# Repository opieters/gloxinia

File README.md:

Gloxinia
========

Open-source release of code and PCB-design files of the Gloxinia platform.

Building the code requires MPLAB X 1.35 or above and KiCAD 5.0.2 or above. 

Citing
------

If you use this code for a scientific publication, please consider citing our paper [_Gloxinia—An Open-Source Sensing Platform to Monitor the Dynamic Responses of Plants_](https://doi.org/10.3390/s20113055).

Licence
-------

GNU GPLv3 4.0

A copy of the licence can be found in `LICENCE`.

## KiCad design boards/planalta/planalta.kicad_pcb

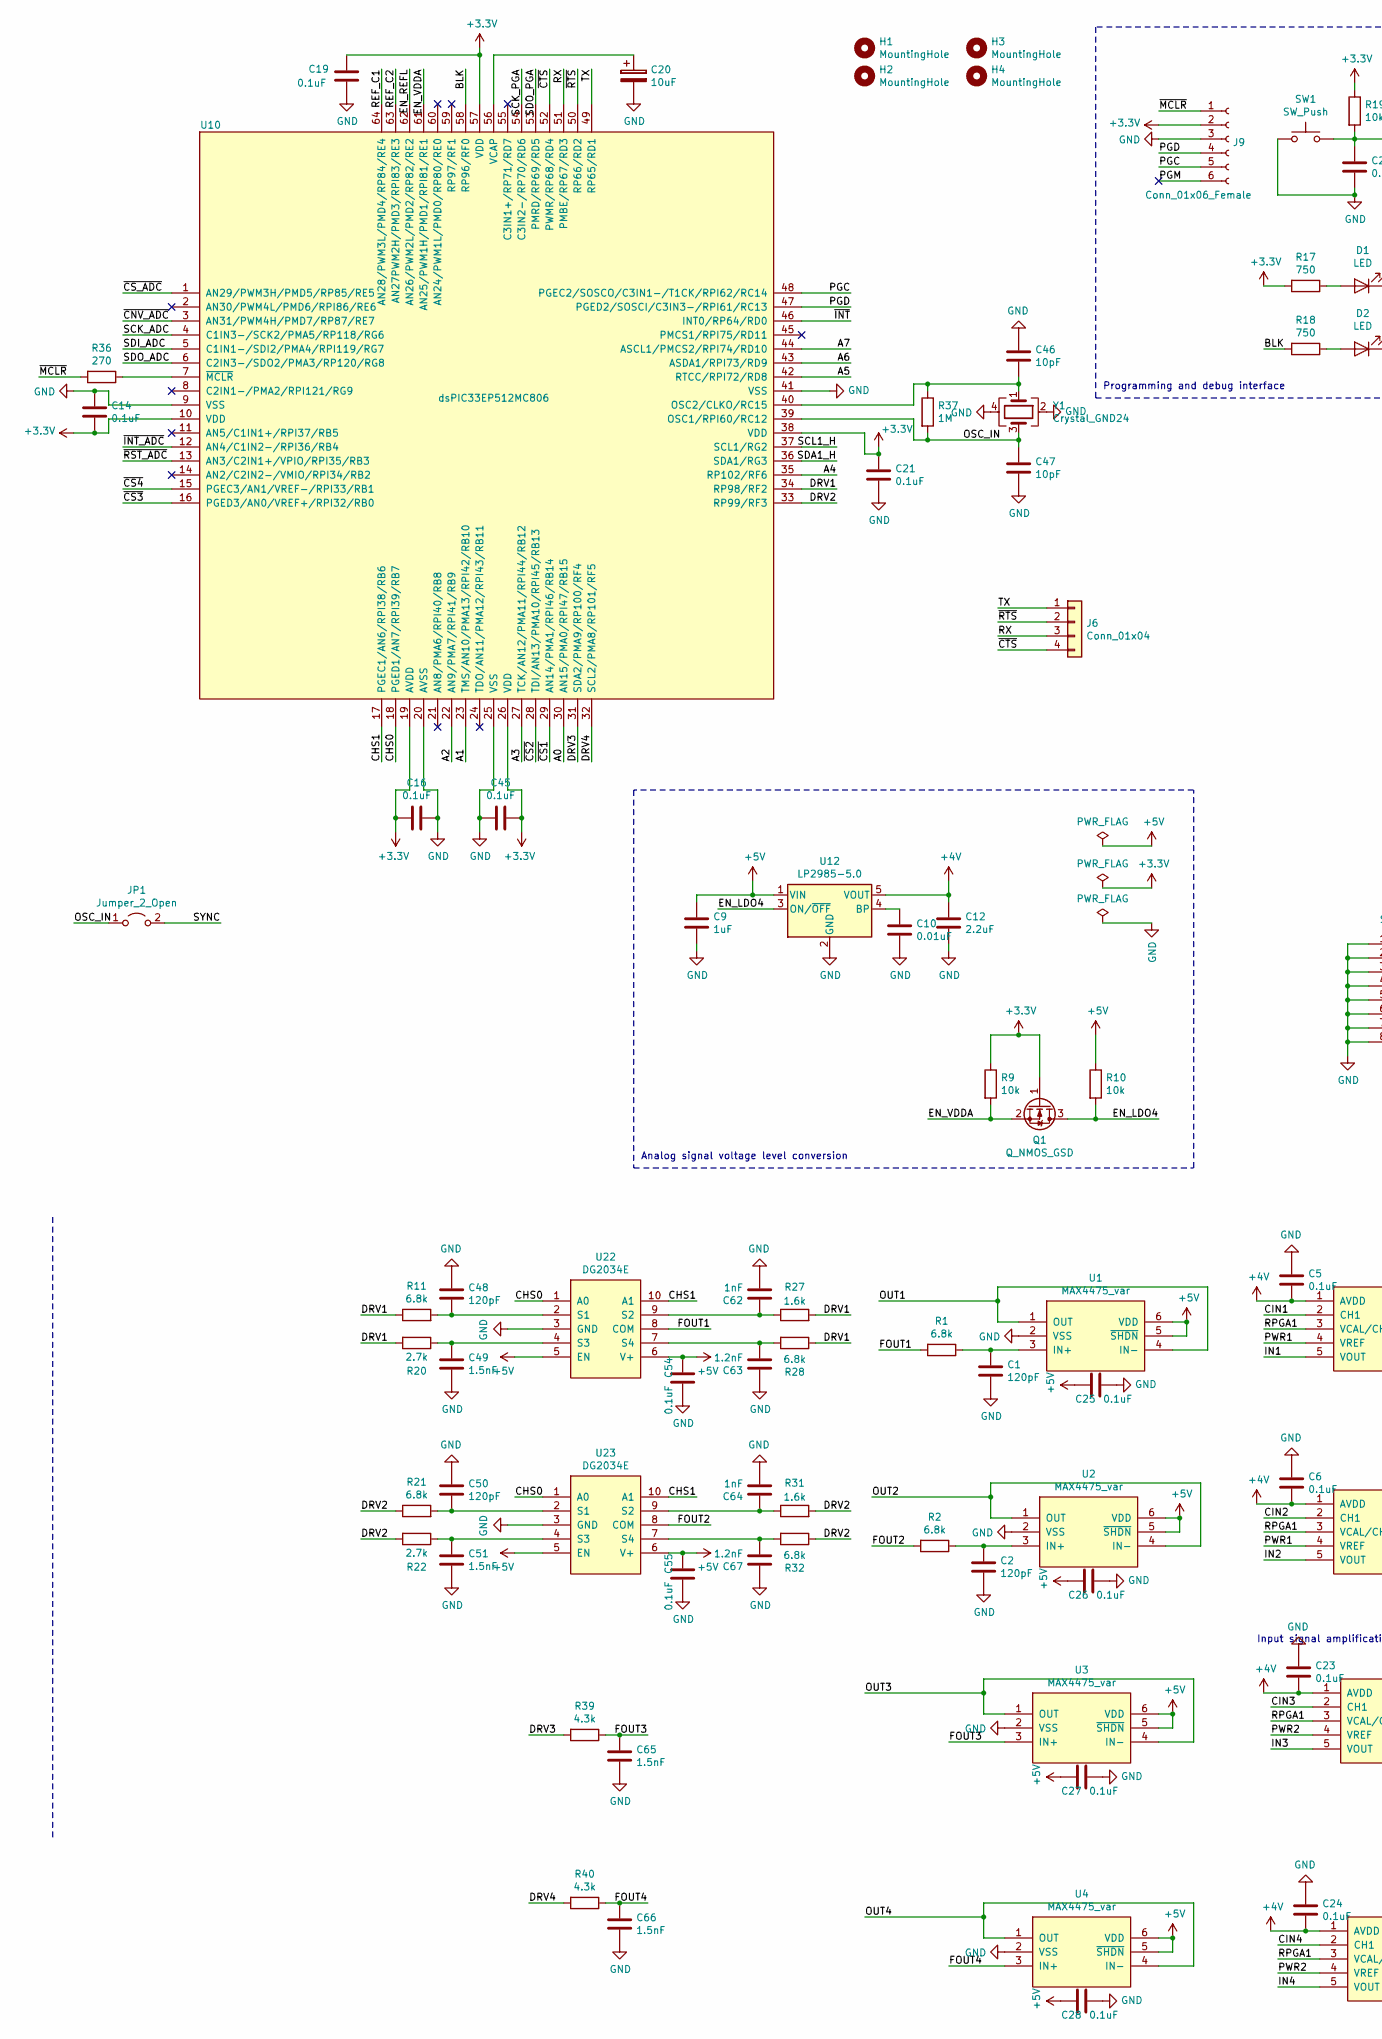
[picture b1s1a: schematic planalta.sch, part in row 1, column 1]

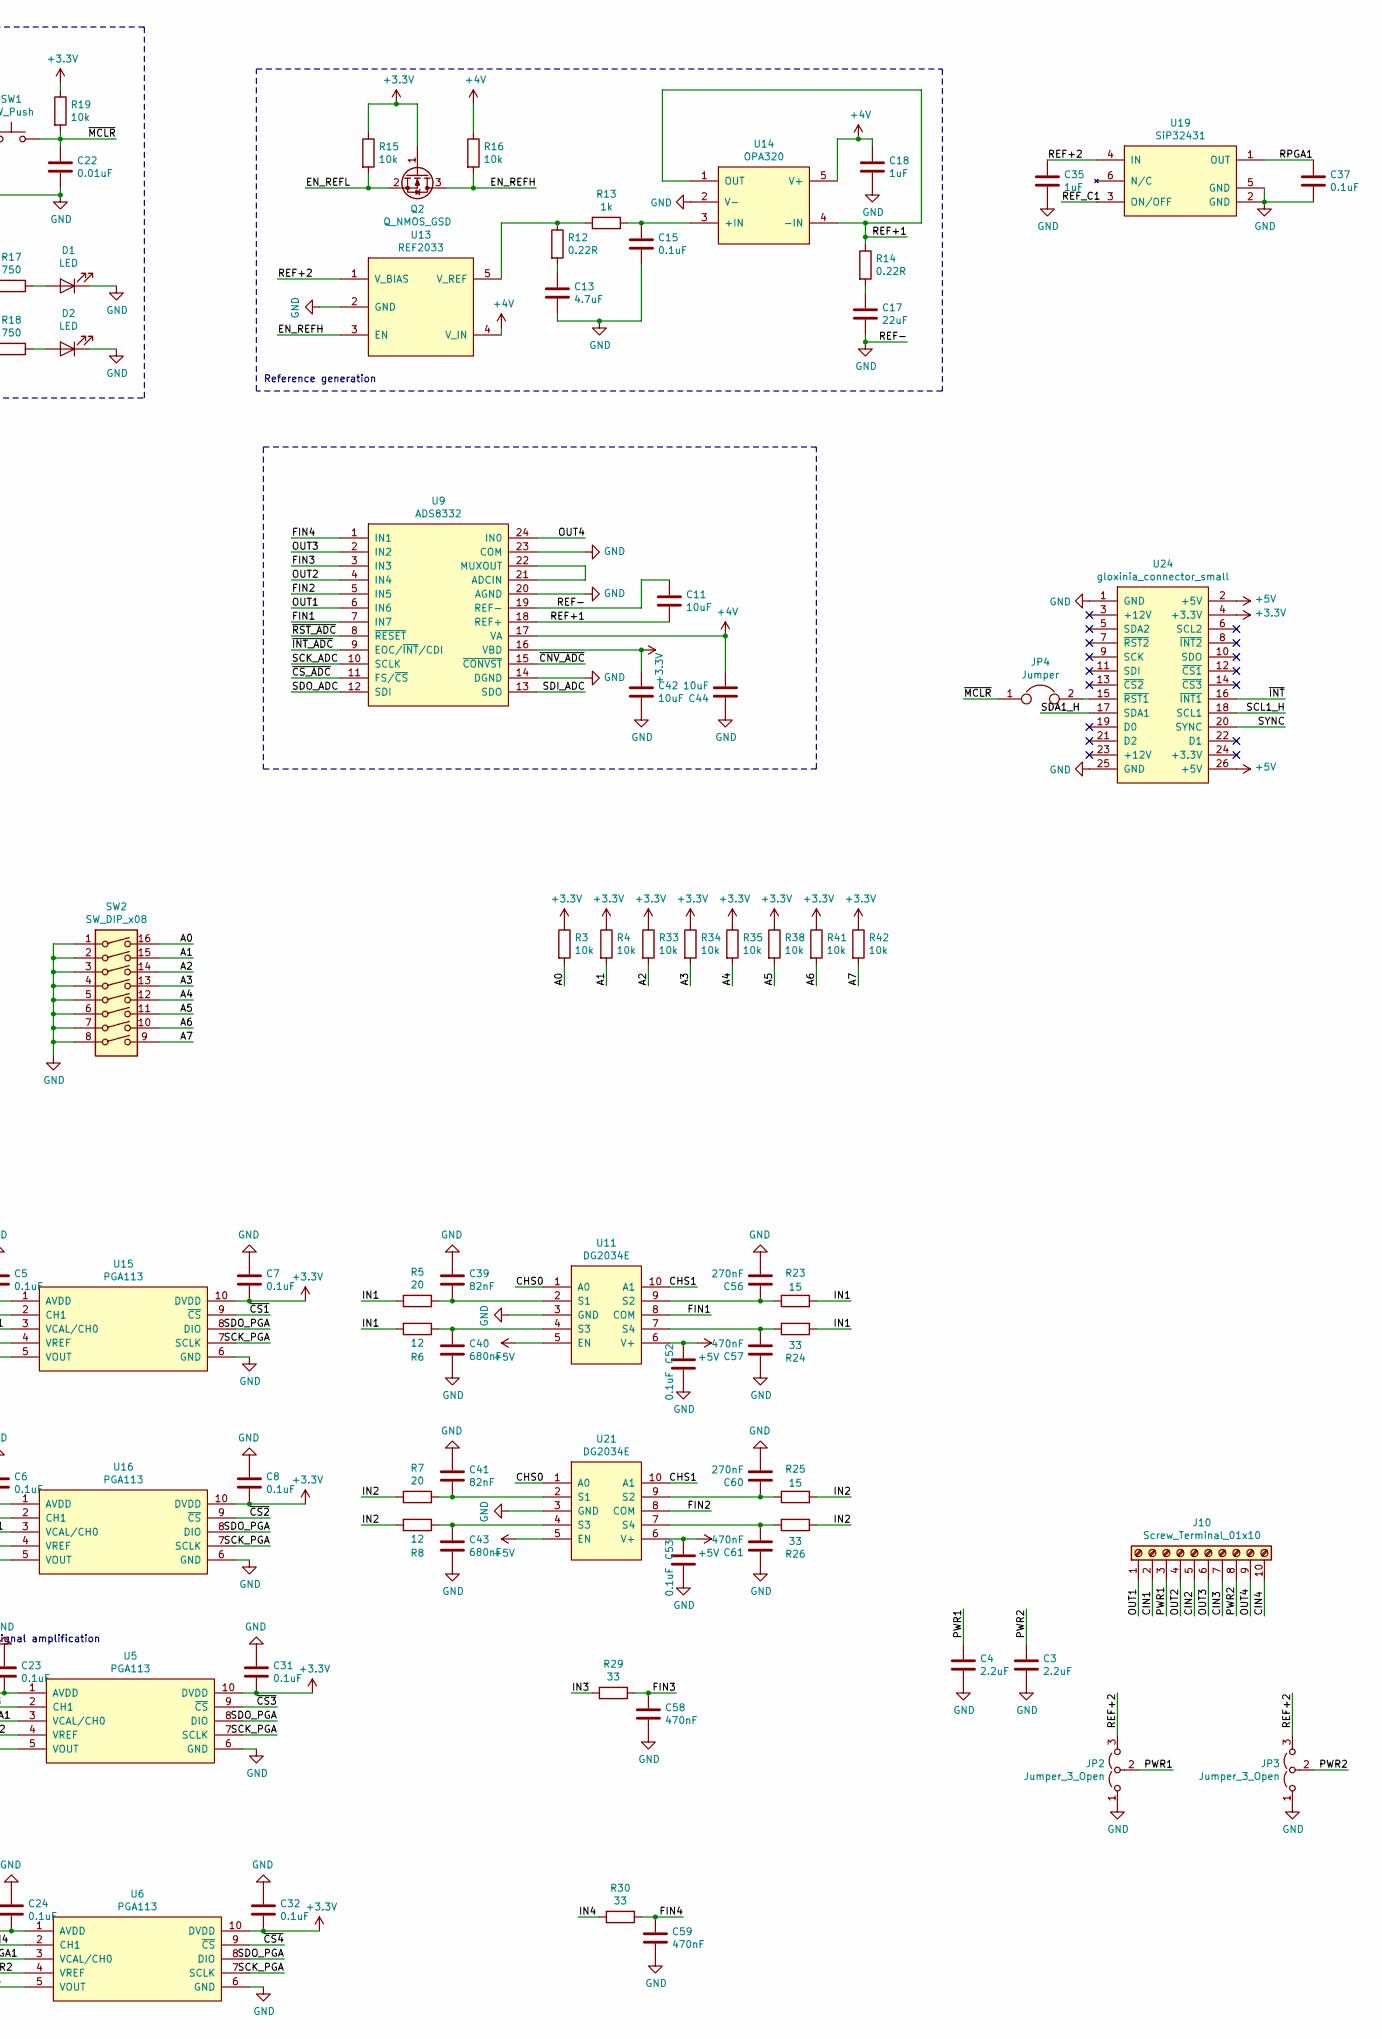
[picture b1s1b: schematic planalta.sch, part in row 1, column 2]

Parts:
C1, C2, C48, C50: 120pF; C_0603_1608Metric; Mouser 80-C0603C121J5GAC
C3, C4, C12: 2.2uF; C_1206_3216Metric; Mouser 791-1206X225K250CT
C5, C6, C7, C8, C14, C15, C16, C19, C21, C23, C24, C25, C26, C27, C28, C31, C32, C37, C45, C52, C53, C54, C55: 0.1uF; C_0603_1608Metric; Mouser 710-885012206071
C9, C18, C35: 1uF; C_0603_1608Metric; Mouser 81-GCM188R71C105K64D
C10, C22: 0.01uF; C_0603_1608Metric; Mouser 81-GRM033C81E103KE4E
C11, C20, C42, C44: 10uF; C_1210_3225Metric; Mouser 963-TMK325BJ106KM-P
C13: 4.7uF; C_1206_3216Metric; Mouser 81-GCG31CR71E475JA1L
C17: 22uF; C_1206_3216Metric; Mouser 963-TMK316BBJ226ML-T
C39, C41: 82nF; C_0603_1608Metric; Mouser 80-C0603C823J3R
C40, C43: 680nF; C_0603_1608Metric; Mouser 710-885012206051
C46, C47: 10pF; C_0603_1608Metric; Mouser 603-CC603FRNPO9BN100
C49, C51, C65, C66: 1.5nF; C_0603_1608Metric; Mouser 710-885012206035
C56, C60: 270nF; C_0603_1608Metric; Mouser 80-C0603C274K8P
C57, C58, C59, C61: 470nF; C_0603_1608Metric; Mouser 710-885012206075
C62, C64: 1nF; C_0603_1608Metric; Mouser 963-TMK325B7105KD-T
C63, C67: 1.2nF; C_0603_1608Metric; Mouser 81-GRM1885C1H122JA01
D1, D2: LED; LED_0603_1608Metric; Mouser 78-TLMS1000
H1, H2, H3, H4: MountingHole; MountingHole_3.2mm_M3
J6: Conn_01x04; PinHeader_1x04_P2.54mm_Vertical
J9: Conn_01x06_Female; PinSocket_1x06_P2.54mm_Vertical
J10: Screw_Terminal_01x10; Header-P5.00mm-10C; Mouser TB003-500-P10BE
JP1: Jumper_2_Open; SolderJumper-2_P1.3mm_Open_Pad1.0x1.5mm
JP2, JP3: Jumper_3_Open; SolderJumper-3_P1.3mm_Open_RoundedPad1.0x1.5mm
JP4: Jumper; SolderJumper-2_P1.3mm_Open_RoundedPad1.0x1.5mm
Q1, Q2: Q_NMOS_GSD; SOT-23; Mouser 512-BSS138
R1, R2, R11, R21, R28, R32: 6.8k; R_0603_1608Metric; Mouser 667-ERJ-3RBD6801V
R3, R4, R9, R10, R15, R16, R19, R33, R34, R35, R38, R41, R42: 10k; R_0603_1608Metric; Mouser 284-APC0603B10K0N
R5, R7: 20; R_0603_1608Metric; Mouser 71-CRCW060320R0FKEAC
R6, R8: 12; R_0603_1608Metric; Mouser 667-ERJ-3EKF15R0V
R12, R14: 0.22R; R_0603_1608Metric; Mouser 667-ERJ-3RQFR22V
R13: 1k; R_0603_1608Metric; Mouser 652-CR0603-FX1001HLF
R17, R18: 750; R_0603_1608Metric; Mouser 603-RC0603FR-07750RL
R20, R22: 2.7k; R_0603_1608Metric; Mouser 603-AC0603FR-102K7L
R23, R25: 15; R_0603_1608Metric; Mouser 667-ERJ-3EKF15R0V
R24, R26, R29, R30: 33; R_0603_1608Metric; Mouser 71-CRCW060333R0FKEAC
R27, R31: 1.6k; R_0603_1608Metric; Mouser 603-RC0603FR-071K6L
R36: 270; R_0603_1608Metric; Mouser 603-RC0603FR-07270RL
R37: 1M; R_0603_1608Metric; Mouser 603-RC0603FR-101ML
R39, R40: 4.3k; R_0603_1608Metric
SW1: SW_Push; SW_SPST_KMR2; Mouser 611-KMR621NGLFS
SW2: SW_DIP_x08; SW_DIP_SPSTx08_Slide_Omron_A6H-8101_W6.15mm_P1.27mm; Mouser 653-A6H-8101
U1, U2, U3, U4: MAX4475_var; SOT-23-6; Mouser 700-MAX4475AUT+T
U5, U6, U15, U16: PGA113; MSOP-10_3x3mm_P0.5mm; Mouser 595-PGA113AIDGSR
U9: ADS8332; TSSOP-24_4.4x7.8mm_P0.65mm; Mouser 595-ADS8332IBPWR
U10: dsPIC33EP512MC806; TQFP-64_10x10mm_P0.5mm; Mouser 579-33EP512MC806IPT
U11, U21, U22, U23: DG2034E; MSOP-10_3x3mm_P0.5mm; Mouser 78-DG2034EDQ-T1-GE3
U12: LP2985-5.0; SOT-23-5; Mouser 926-LP2985IM540NOPB
U13: REF2033; SOT-23-5; Mouser 595-REF2033AIDDCR
U14: OPA320; SOT-23-5; Mouser 595-OPA320AIDBVR
U19: SiP32431; SOT-363_SC-70-6; Mouser 781-SIP32431DR3-GE3
U24: gloxinia_connector_small; PinHeader_2x13_P2.54mm_Vertical; Mouser 200-SSQ11303TD
Y1: Crystal_GND24; Crystal_SMD_Abracon_ABM3B-4Pin_5.0x3.2mm; Mouser 520-80-10-30B-CWNT

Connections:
+3V3: C7.2, C8.2, C14.2, C16.2, C19.1, C21.1, C31.2, C32.2, C42.1, C45.1, J9.2, Q1.1 (G), Q2.1 (G), R3.1, R4.1, R9.1, R15.1, R17.2, R19.1, R33.1, R34.1, R35.1, R38.1, R41.1, R42.1, U5.10 (DVDD), U6.10 (DVDD), U9.16 (VBD), U10.10 (VDD), U10.19 (AVDD), U10.26 (VDD), U10.38 (VDD), U10.57 (VDD), U15.10 (DVDD), U16.10 (DVDD), U24.4 (+3.3V)
+4V: C5.2, C6.2, C12.1, C18.1, C23.2, C24.2, C44.2, R16.1, U5.1 (AVDD), U6.1 (AVDD), U9.17 (VA), U12.5 (VOUT), U13.4 (V_IN), U14.5 (V+), U15.1 (AVDD), U16.1 (AVDD)
+5V: C9.1, C25.2, C26.2, C27.2, C28.2, C52.2, C53.2, C54.2, C55.2, R10.1, U1.5 (~SHDN), U1.6 (VDD), U2.5 (~SHDN), U2.6 (VDD), U3.5 (~SHDN), U3.6 (VDD), U4.5 (~SHDN), U4.6 (VDD), U11.5 (EN), U11.6 (V+), U12.1 (VIN), U21.5 (EN), U21.6 (V+), U22.5 (EN), U22.6 (V+), U23.5 (EN), U23.6 (V+), U24.2 (+5V), U24.26 (+5V)
/A0: R3.2, SW2.16, U10.30 (AN15/PMA0/RPI47/RB15)
/A1: R4.2, SW2.15, U10.23 (TMS/AN10/PMA13/RPI42/RB10)
/A2: R33.2, SW2.14, U10.22 (AN9/PMA7/RPI41/RB9)
/A3: R34.2, SW2.13, U10.27 (TCK/AN12/PMA11/RPI44/RB12)
/A4: R35.2, SW2.12, U10.35 (RP102/RF6)
/A5: R38.2, SW2.11, U10.42 (RTCC/RPI72/RD8)
/A6: R41.2, SW2.10, U10.43 (ASDA1/RPI73/RD9)
/A7: R42.2, SW2.9, U10.44 (ASCL1/PMCS2/RPI74/RD10)
/BLK: R18.2, U10.58 (RP96/RF0)
/CHS0: U10.18 (PGED1/AN7/RPI39/RB7), U11.1 (A0), U21.1 (A0), U22.1 (A0), U23.1 (A0)
/CHS1: U10.17 (PGEC1/AN6/RPI38/RB6), U11.10 (A1), U21.10 (A1), U22.10 (A1), U23.10 (A1)
/CIN1: J10.2, U15.2 (CH1)
/CIN2: J10.5, U16.2 (CH1)
/CIN3: J10.7, U5.2 (CH1)
/CIN4: J10.10, U6.2 (CH1)
/DRV1: R11.1, R20.2, R27.2, R28.1, U10.34 (RP98/RF2)
/DRV2: R21.1, R22.2, R31.2, R32.1, U10.33 (RP99/RF3)
/DRV3: R39.2, U10.31 (SDA2/PMA9/RP100/RF4)
/DRV4: R40.2, U10.32 (SCL2/PMA8/RP101/RF5)
/EN_LDO4: Q1.3 (D), R10.2, U12.3 (ON/~OFF~)
/EN_REFH: Q2.3 (D), R16.2, U13.3 (EN)
/EN_REFL: Q2.2 (S), R15.2, U10.62 (AN26/PWM2L/PMD2/RP82/RE2)
/EN_VDDA: Q1.2 (S), R9.2, U10.61 (AN25/PWM1H/PMD1/RPI81/RE1)
/FIN1: U9.7 (IN7), U11.8 (COM)
/FIN2: U9.5 (IN5), U21.8 (COM)
/FIN3: C58.1, R29.1, U9.3 (IN3)
/FIN4: C59.1, R30.1, U9.1 (IN1)
/FOUT1: R1.2, U22.8 (COM)
/FOUT2: R2.2, U23.8 (COM)
/FOUT3: C65.1, R39.1, U3.3 (IN+)
/FOUT4: C66.1, R40.1, U4.3 (IN+)
/IN1: R5.1, R6.2, R23.2, R24.1, U15.5 (VOUT)
/IN2: R7.1, R8.2, R25.2, R26.1, U16.5 (VOUT)
/IN3: R29.2, U5.5 (VOUT)
/IN4: R30.2, U6.5 (VOUT)
/OSC_IN: C47.1, JP1.1 (A), R37.2, U10.39 (OSC1/RPI60/RC12), Y1.3
/OUT1: J10.1, U1.1 (OUT), U1.4 (IN-), U9.6 (IN6)
/OUT2: J10.4, U2.1 (OUT), U2.4 (IN-), U9.4 (IN4)
/OUT3: J10.6, U3.1 (OUT), U3.4 (IN-), U9.2 (IN2)
/OUT4: J10.9, U4.1 (OUT), U4.4 (IN-), U9.24 (IN0)
/PGC: J9.5, U10.48 (PGEC2/SOSCO/C3IN1-/T1CK/RPI62/RC14)
/PGD: J9.4, U10.47 (PGED2/SOSCI/C3IN3-/RPI61/RC13)
/PGM: J9.6
/PWR1: C4.1, J10.3, JP2.2 (C), U15.4 (VREF), U16.4 (VREF)
/PWR2: C3.1, J10.8, JP3.2 (C), U5.4 (VREF), U6.4 (VREF)
/REF+1: C11.2, R14.1, U9.18 (REF+), U14.1 (OUT), U14.4 (-IN)
/REF+2: C35.1, JP2.3 (B), JP3.3 (B), U13.1 (V_BIAS), U19.4 (IN)
/REF_C1: U10.64 (AN28/PWM3L/PMD4/RP84/RE4), U19.3 (ON/OFF)
/REF_C2: U10.63 (AN27PWM2H/PMD3/RPI83/RE3)
/RPGA1: C37.1, U5.3 (VCAL/CH0), U6.3 (VCAL/CH0), U15.3 (VCAL/CH0), U16.3 (VCAL/CH0), U19.1 (OUT)
/RX: J6.3, U10.51 (PMBE/RP67/RD3)
/SCK_ADC: U9.10 (SCLK), U10.4 (C1IN3-/SCK2/PMA5/RP118/RG6)
/SCK_PGA: U5.7 (SCLK), U6.7 (SCLK), U10.54 (C3IN2-/RP70/RD6), U15.7 (SCLK), U16.7 (SCLK)
/SCL1_H: U10.37 (SCL1/RG2), U24.18 (SCL1)
/SDA1_H: U10.36 (SDA1/RG3), U24.17 (SDA1)
/SDI_ADC: U9.13 (SDO), U10.5 (C1IN1-/SDI2/PMA4/RPI119/RG7)
/SDO_ADC: U9.12 (SDI), U10.6 (C2IN3-/SDO2/PMA3/RP120/RG8)
/SDO_PGA: U5.8 (DIO), U6.8 (DIO), U10.53 (PMRD/RP69/RD5), U15.8 (DIO), U16.8 (DIO)
/SYNC: JP1.2 (B), U24.20 (SYNC)
/TX: J6.1, U10.49 (RP65/RD1)
/~CNV_ADC: U9.15 (~CONVST), U10.3 (AN31/PWM4H/PMD7/RP87/RE7)
/~CS1: U10.29 (AN14/PMA1/RPI46/RB14), U15.9 (~CS)
/~CS2: U10.28 (TDI/AN13/PMA10/RPI45/RB13), U16.9 (~CS)
/~CS3: U5.9 (~CS), U10.16 (PGED3/AN0/VREF+/RPI32/RB0)
/~CS4: U6.9 (~CS), U10.15 (PGEC3/AN1/VREF-/RPI33/RB1)
/~CS_ADC: U9.11 (FS/~CS), U10.1 (AN29/PWM3H/PMD5/RP85/RE5)
/~CTS: J6.4, U10.52 (PWMR/RP68/RD4)
/~INT: U10.46 (INT0/RP64/RD0), U24.16 (~INT1)
/~INT_ADC: U9.9 (EOC/~INT~/CDI), U10.12 (AN4/C1IN2-/RPI36/RB4)
/~MCLR: C22.1, J9.1, JP4.1, R19.2, R36.2, SW1.2
/~RST_ADC: U9.8 (~RESET), U10.13 (AN3/C2IN1+/VPIO/RPI35/RB3)
/~RTS: J6.2, U10.50 (RP66/RD2)
GND: C1.2, C2.2, C3.2, C4.2, C5.1, C6.1, C7.1, C8.1, C9.2, C10.2, C11.1, C12.2, C13.2, C14.1, C15.2, C16.1, C17.2, C18.2, C19.2, C20.2, C21.2, C22.2, C23.1, C24.1, C25.1, C26.1, C27.1, C28.1, C31.1, C32.1, C35.2, C37.2, C39.1, C40.2, C41.1, C42.2, C43.2, C44.1, C45.2, C46.1, C47.2, C48.1, C49.2, C50.1, C51.2, C52.1, C53.1, C54.1, C55.1, C56.2, C57.1, C58.2, C59.2, C60.2, C61.1, C62.2, C63.1, C64.2, C65.2, C66.2, C67.1, D1.1 (K), D2.1 (K), J9.3, JP2.1 (A), JP3.1 (A), SW1.1, SW2.1, SW2.2, SW2.3, SW2.4, SW2.5, SW2.6, SW2.7, SW2.8, U1.2 (VSS), U2.2 (VSS), U3.2 (VSS), U4.2 (VSS), U5.6 (GND), U6.6 (GND), U9.14 (DGND), U9.19 (REF-), U9.20 (AGND), U9.23 (COM), U10.9 (VSS), U10.20 (AVSS), U10.25 (VSS), U10.41 (VSS), U11.3 (GND), U12.2 (GND), U13.2 (GND), U14.2 (V-), U15.6 (GND), U16.6 (GND), U19.2 (GND), U19.5 (GND), U21.3 (GND), U22.3 (GND), U23.3 (GND), U24.1 (GND), U24.25 (GND), Y1.2, Y1.4
unnamed: C1.1, R1.1, U1.3 (IN+)
unnamed: C2.1, R2.1, U2.3 (IN+)
unnamed: C10.1, U12.4 (BP)
unnamed: C13.1, R12.2
unnamed: C15.1, R13.1, U14.3 (+IN)
unnamed: C17.1, R14.2
unnamed: C20.1, U10.56 (VCAP)
unnamed: C39.2, R5.2, U11.2 (S1)
unnamed: C40.1, R6.1, U11.4 (S3)
unnamed: C41.2, R7.2, U21.2 (S1)
unnamed: C43.1, R8.1, U21.4 (S3)
unnamed: C46.2, R37.1, U10.40 (OSC2/CLKO/RC15), Y1.1
unnamed: C48.2, R11.2, U22.2 (S1)
unnamed: C49.1, R20.1, U22.4 (S3)
unnamed: C50.2, R21.2, U23.2 (S1)
unnamed: C51.1, R22.1, U23.4 (S3)
unnamed: C56.1, R23.1, U11.9 (S2)
unnamed: C57.2, R24.2, U11.7 (S4)
unnamed: C60.1, R25.1, U21.9 (S2)
unnamed: C61.2, R26.2, U21.7 (S4)
unnamed: C62.1, R27.1, U22.9 (S2)
unnamed: C63.2, R28.2, U22.7 (S4)
unnamed: C64.1, R31.1, U23.9 (S2)
unnamed: C67.2, R32.2, U23.7 (S4)
unnamed: D1.2 (A), R17.1
unnamed: D2.2 (A), R18.1
unnamed: JP4.2, U24.15 (~RST1)
unnamed: R12.1, R13.2, U13.5 (V_REF)
unnamed: R36.1, U10.7 (~MCLR)
unnamed: U9.21 (ADCIN), U9.22 (MUXOUT)

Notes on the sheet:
Programming and debug interface
Reference generation
Analog signal voltage level conversion
Input signal amplification

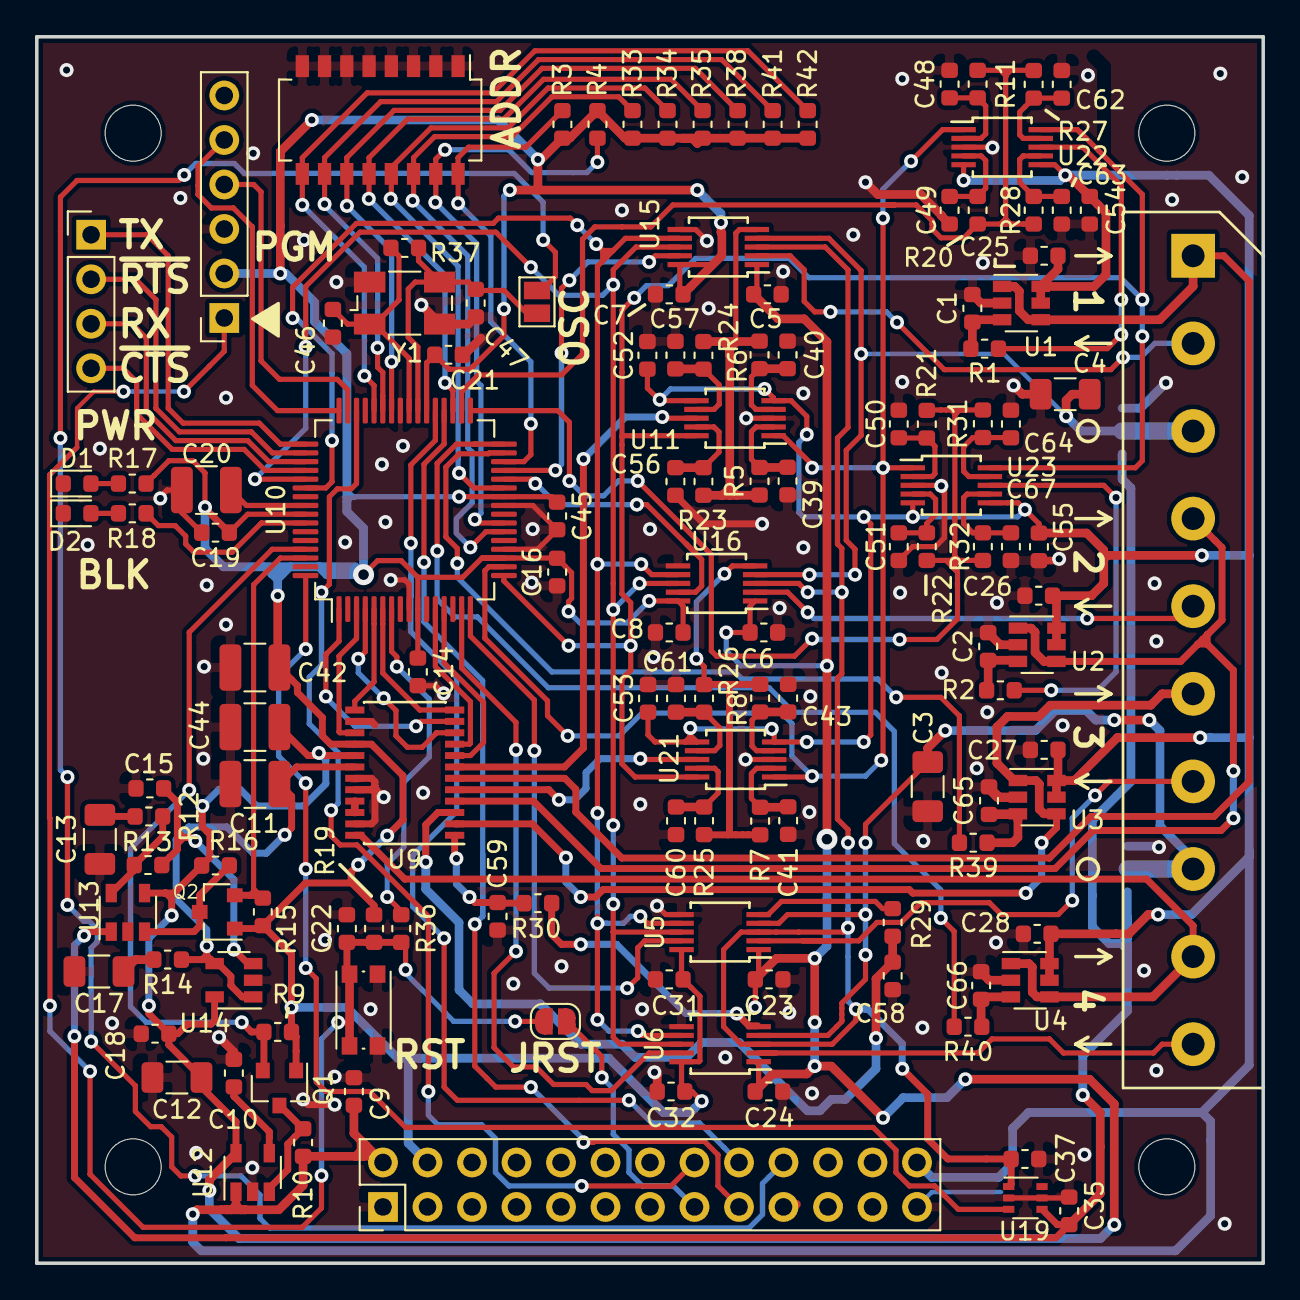
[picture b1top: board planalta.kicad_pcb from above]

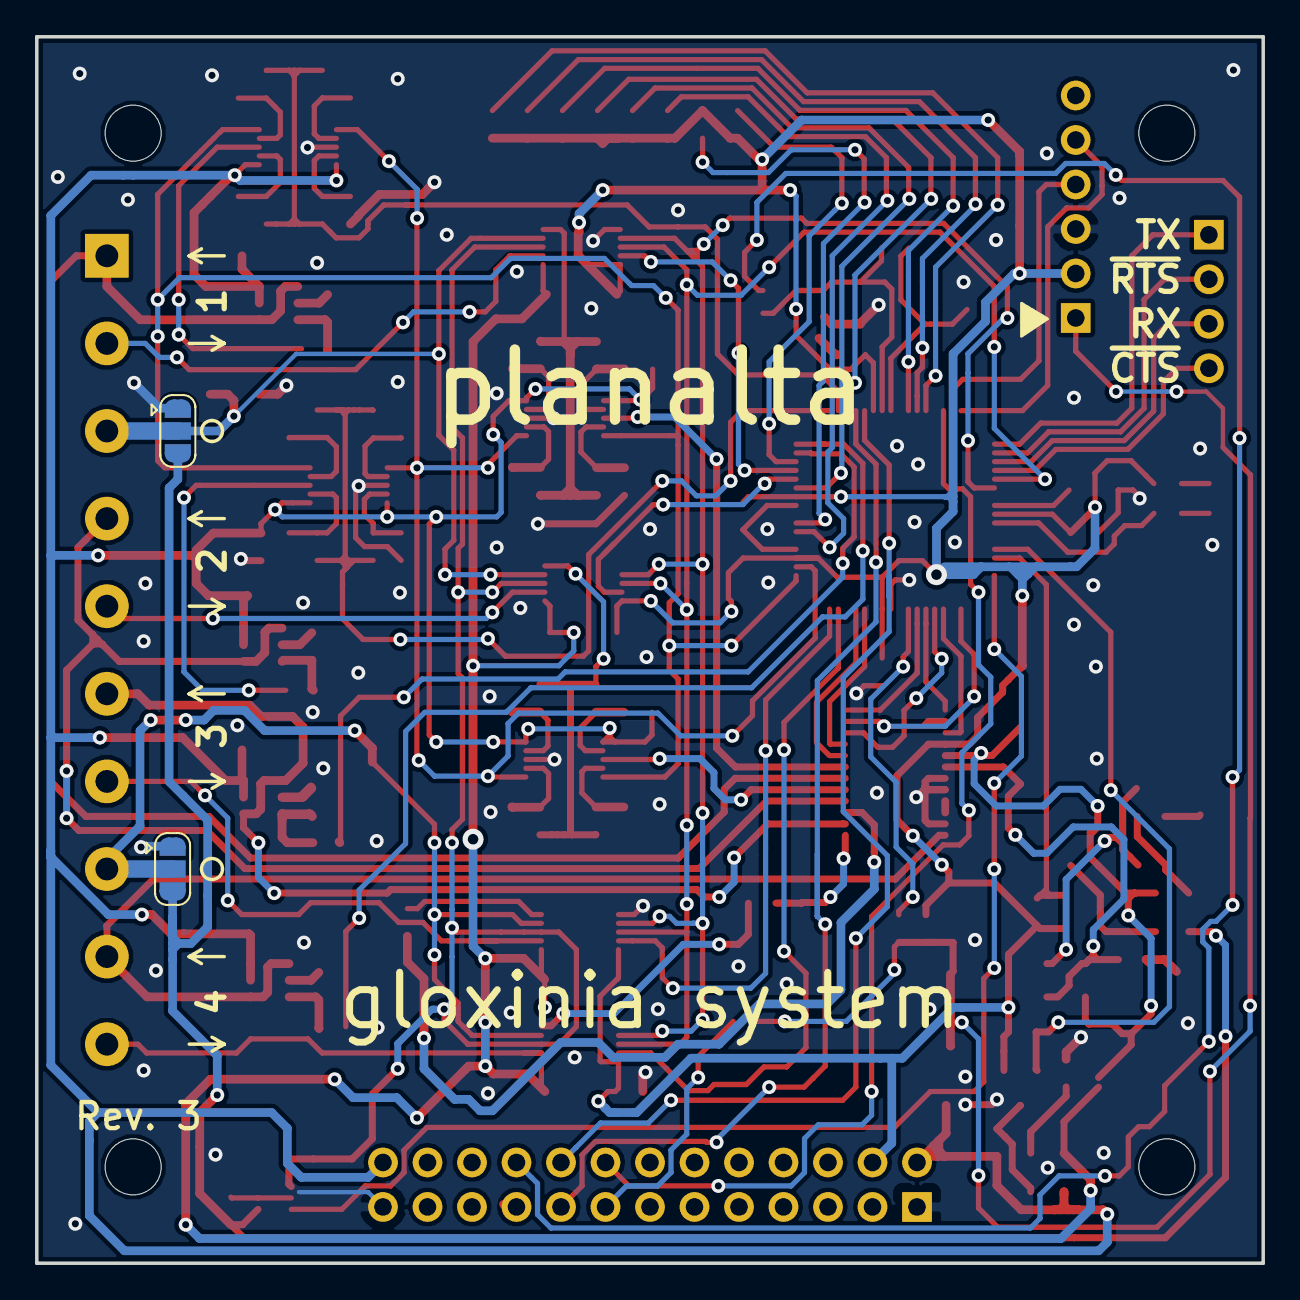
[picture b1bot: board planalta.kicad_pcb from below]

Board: 2 copper layers, 70.0 x 70.0 mm, 140 parts (2 on the bottom side), 104 nets.

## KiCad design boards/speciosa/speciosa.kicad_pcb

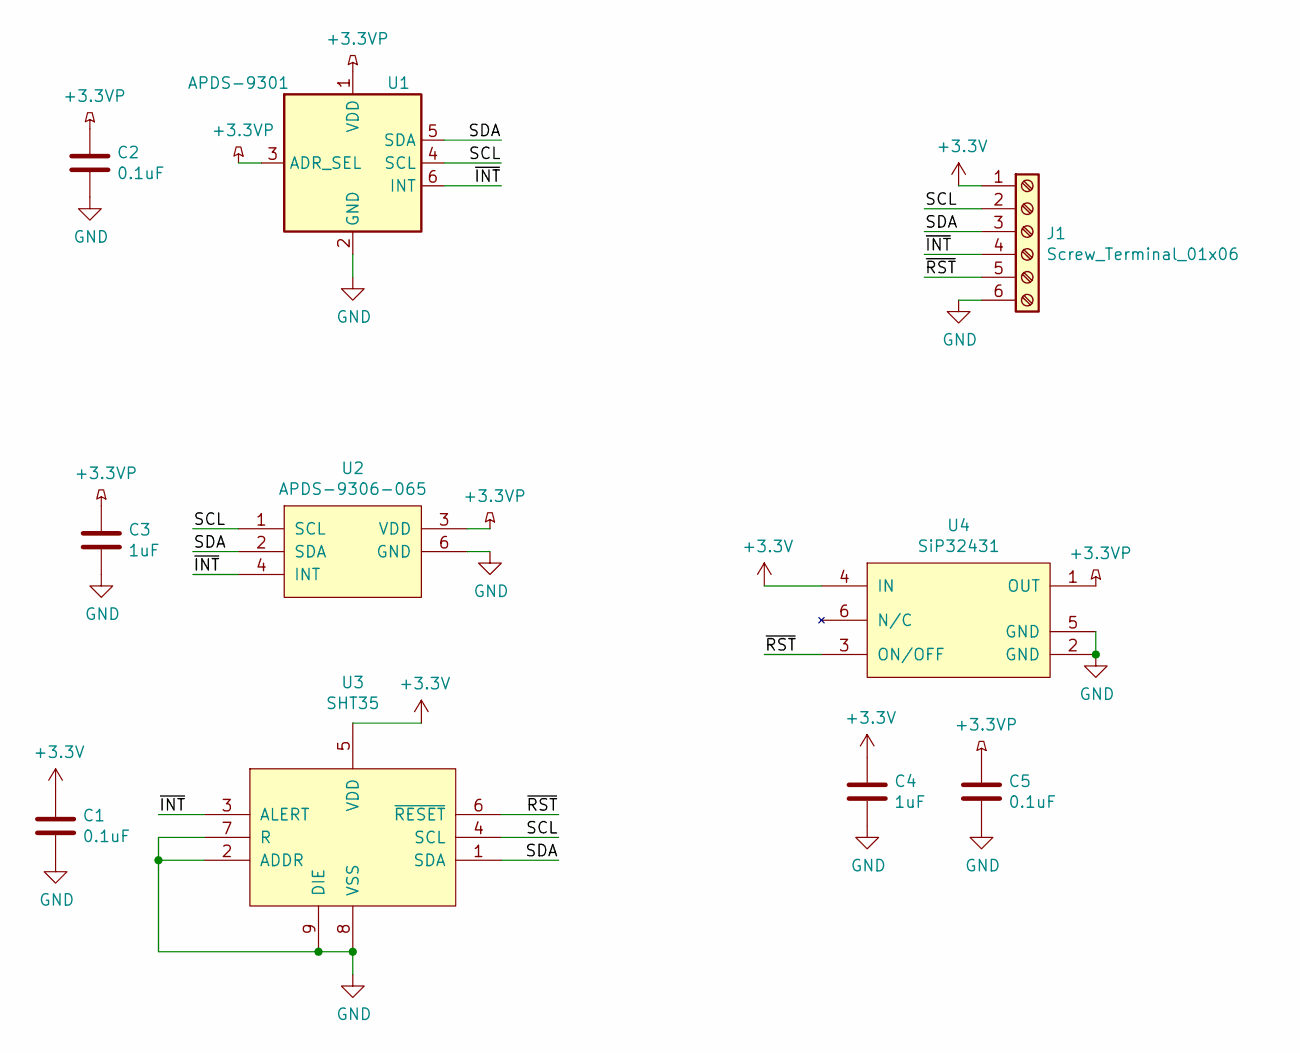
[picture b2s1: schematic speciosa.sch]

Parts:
C1, C2, C5: 0.1uF; C_0603_1608Metric; Mouser 810-CGA3E2X8R1E104K
C3, C4: 1uF; C_0603_1608Metric; Mouser 710-885012106022
J1: Screw_Terminal_01x06; PinHeader_1x06_P2.54mm_Vertical
U1: APDS-9301; Broadcom_APDS-9301; Farnell 2497389
U2: APDS-9306-065; Mouser 630-APDS-9306-065
U3: SHT35; 8P-1EP-DFN_2.5x2.5; Mouser 403-SHT35-DIS-F
U4: SiP32431; SOT-363_SC-70-6; Mouser 781-SIP32431DR3-GE3

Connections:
+3.3VP: C2.1, C3.1, C5.1, U1.1 (VDD), U1.3 (ADR_SEL), U2.3 (VDD), U4.1 (OUT)
+3V3: C1.1, C4.1, J1.1, U3.5 (VDD), U4.4 (IN)
/SCL: J1.2, U1.4 (SCL), U2.1 (SCL), U3.4 (SCL)
/SDA: J1.3, U1.5 (SDA), U2.2 (SDA), U3.1 (SDA)
/~INT: J1.4, U1.6 (INT), U2.4 (INT), U3.3 (ALERT)
/~RST: J1.5, U3.6 (~RESET), U4.3 (ON/OFF)
GND: C1.2, C2.2, C3.2, C4.2, C5.2, J1.6, U1.2 (GND), U2.6 (GND), U3.2 (ADDR), U3.7 (R), U3.8 (VSS), U3.9 (DIE), U4.2 (GND), U4.5 (GND)

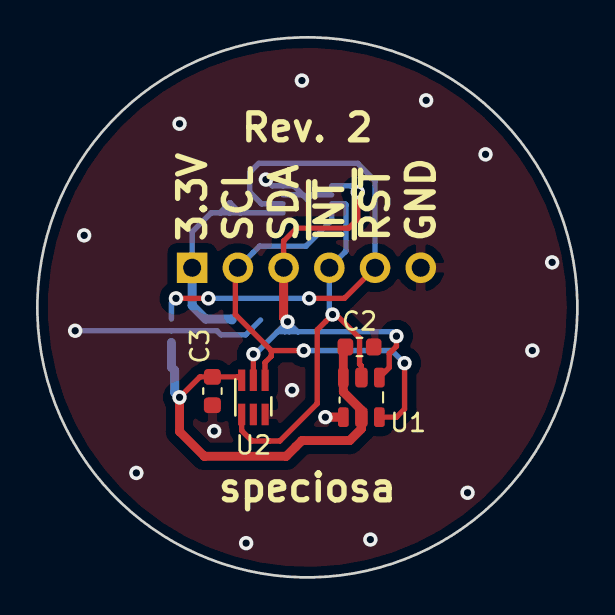
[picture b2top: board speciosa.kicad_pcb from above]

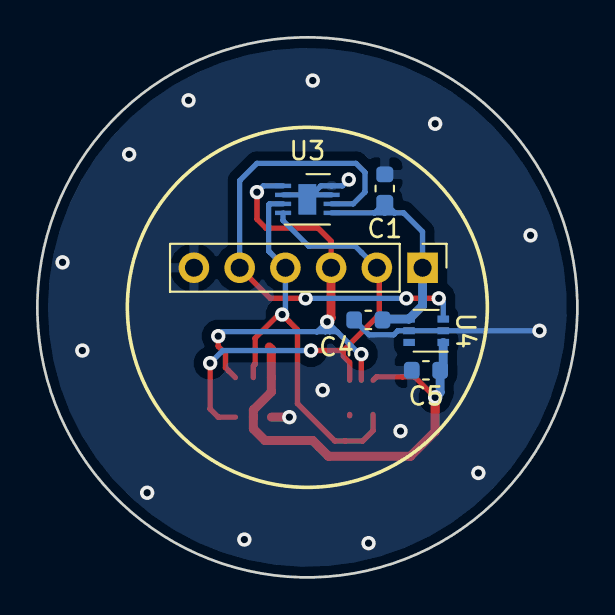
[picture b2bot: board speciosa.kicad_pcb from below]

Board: 2 copper layers, 30.0 x 30.0 mm, 10 parts (6 on the bottom side), 7 nets.
